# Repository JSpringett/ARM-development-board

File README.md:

# ARM Cortex M0 Development Board

This is a simple ARM Cortex M0 development board based around a STM32 MCU.

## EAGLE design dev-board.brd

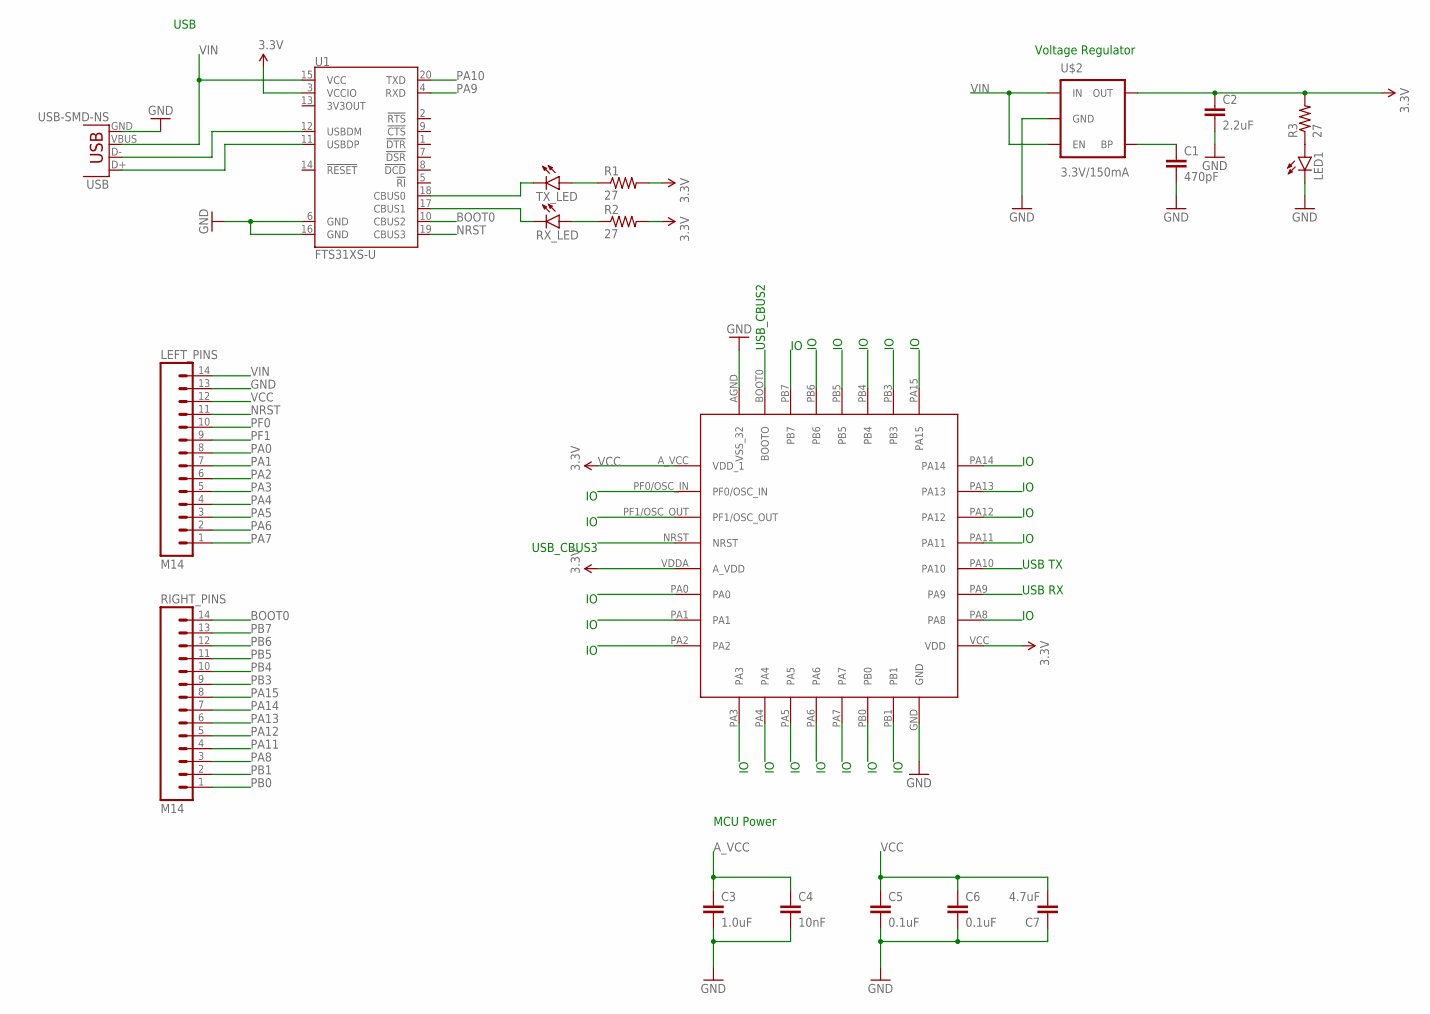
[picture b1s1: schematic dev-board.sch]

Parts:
C1: 470pF; 0603-CAP
C2: 2.2uF; 0603-CAP
C3: 1.0uF; 0603-CAP
C4: 10nF; 0603-CAP
C5, C6: 0.1uF; 0402-CAP
C7: 4.7uF; 0603-CAP
LED1: LED1206; LED-1206
LEFT_PINS: M14; 1X14
R1, R2, R3: 27; 0603
RIGHT_PINS: M14; 1X14
RX_LED: LED1206; LED-1206
TX_LED: LED1206; LED-1206
U1: FTS31XS-U; SSOP20_L
U$1: STM32F051XX; STM32F051-LQFP-32
U$2: 3.3V/150mA; SOT23-5
USB: USB-SMD-NS; USB-MINIB-NOSTOP

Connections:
A_VCC: C3.1, C4.1, U$1.VDDA (A_VDD)
BOOT0: RIGHT_PINS.14, U1.10 (CBUS2), U$1.BOOT0 (BOOTO)
GND: C1.2, C2.2, C3.2, C4.2, C5.2, C6.2, C7.1, LED1.C, LEFT_PINS.13, U1.6 (GND), U1.16 (GND), U$1.AGND (VSS_32), U$1.GND, U$2.2 (GND), USB.GND
unnamed: RX_LED.C, U1.17 (CBUS1)
unnamed: TX_LED.C, U1.18 (CBUS0)
unnamed: R1.1, TX_LED.A
unnamed: R2.1, RX_LED.A
unnamed: LED1.A, R3.1
unnamed: C1.1, U$2.4 (BP)
NRST: LEFT_PINS.11, U1.19 (CBUS3), U$1.NRST
PA0: LEFT_PINS.8, U$1.PA0
PA1: LEFT_PINS.7, U$1.PA1
PA2: LEFT_PINS.6, U$1.PA2
PA3: LEFT_PINS.5, U$1.PA3
PA4: LEFT_PINS.4, U$1.PA4
PA5: LEFT_PINS.3, U$1.PA5
PA6: LEFT_PINS.2, U$1.PA6
PA7: LEFT_PINS.1, U$1.PA7
PA8: RIGHT_PINS.3, U$1.PA8
PA9: U1.4 (RXD), U$1.PA9
PA10: U1.20 (TXD), U$1.PA10
PA11: RIGHT_PINS.4, U$1.PA11
PA12: RIGHT_PINS.5, U$1.PA12
PA13: RIGHT_PINS.6, U$1.PA13
PA14: RIGHT_PINS.7, U$1.PA14
PA15: RIGHT_PINS.8, U$1.PA15
PB0: RIGHT_PINS.1, U$1.PB0
PB1: RIGHT_PINS.2, U$1.PB1
PB3: RIGHT_PINS.9, U$1.PB3
PB4: RIGHT_PINS.10, U$1.PB4
PB5: RIGHT_PINS.11, U$1.PB5
PB6: RIGHT_PINS.12, U$1.PB6
PB7: RIGHT_PINS.13, U$1.PB7
PF0: LEFT_PINS.10, U$1.PF0/OSC_IN
PF1: LEFT_PINS.9, U$1.PF1/OSC_OUT
USB_D+: U1.11 (USBDP), USB.D+
USB_D-: U1.12 (USBDM), USB.D-
VCC: C2.1, C5.1, C6.1, C7.2, LEFT_PINS.12, R1.2, R2.2, R3.2, U1.3 (VCCIO), U$1.A_VCC (VDD_1), U$1.VCC (VDD), U$2.5 (OUT)
VIN: LEFT_PINS.14, U1.15 (VCC), U$2.1 (IN), U$2.3 (EN), USB.VBUS

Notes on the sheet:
Voltage Regulator
MCU Power
USB TX
USB RX
USB_CBUS3
USB_CBUS2
USB

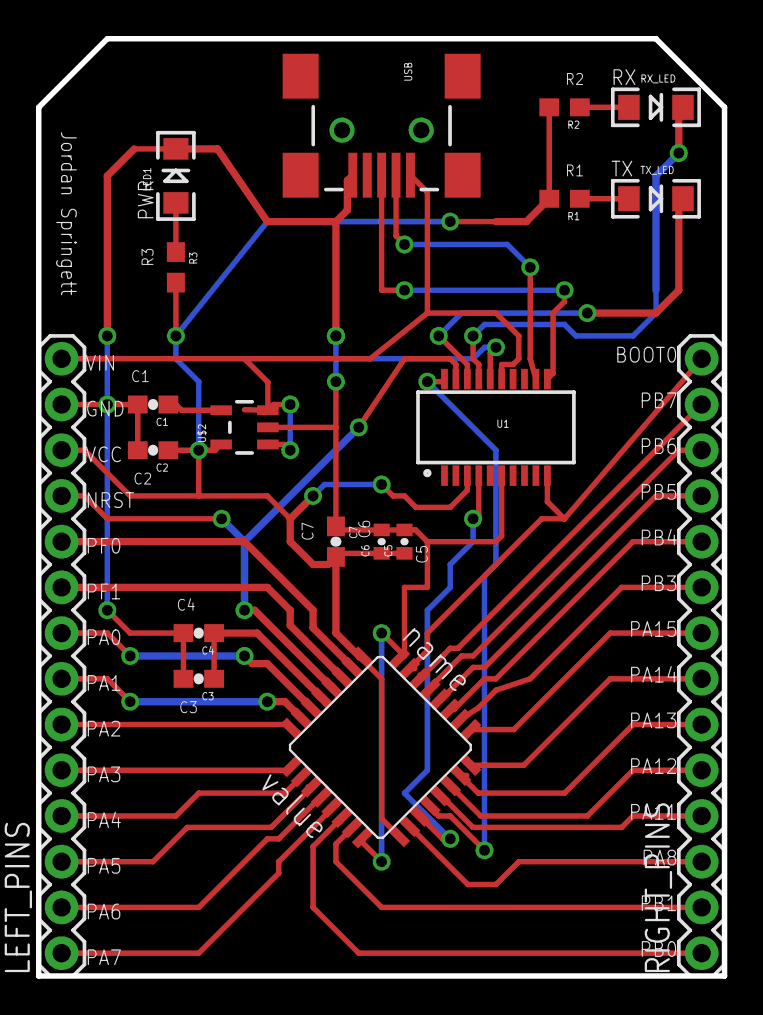
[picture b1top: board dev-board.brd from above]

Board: 2 copper layers, 38.1 x 52.1 mm, 19 parts (0 on the bottom side), 39 nets.

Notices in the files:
parts and their libraries:
SparkFun-Capacitors: Licensing: Creative Commons ShareAlike 4.0 International - https://creativecommons.org/licenses/by-sa/4.0
